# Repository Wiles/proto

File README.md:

# proto

## usb

Breakout board for Molex Micro USB (series 47346).

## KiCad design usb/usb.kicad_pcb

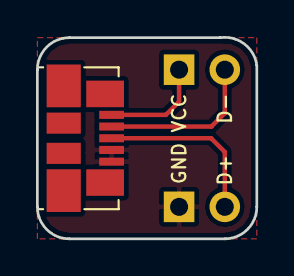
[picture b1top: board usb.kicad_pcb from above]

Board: 2 copper layers, 12.2 x 11.2 mm, 3 parts (0 on the bottom side), 4 nets.

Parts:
J1: USB_B; USB_Micro-B_Molex_47346-0001
J2, J3: CONN_01X02; Pin_Header_Straight_1x02_Pitch2.54mm

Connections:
/D+: J1.3, J2.2
/D-: J1.2, J3.2
GND: J1.4, J1.5, J2.1
VCC: J1.1, J3.1

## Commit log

2017-06-18 Rev. 1 USB breakout
